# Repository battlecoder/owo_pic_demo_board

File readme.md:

# OWO PIC Demo Board
This is a very simple demo board I designed around one of my favorite microcontrollers: The PIC 16F628A from Microchip.
I also wrote a small "framework" in asm for it, that handles the display, buttons, serial comm, text scrolling, etc, and I've included a simple implementation of Tetris as an example of its usage.

You'll find the schematic and board layout (KiCad) of the *OWO board* in the **/board** folder. There's a lot that can be improved but it works as it is. The demo code and framework/boilerplate is in the **/asm_demo_code** directory.

You can see a video of one the early builds of the Tetris demo running on the board:
<blockquote class="twitter-tweet"><p lang="en" dir="ltr">Tetris implemented in assembly on the PIC16F628A demo board I designed a few months ago. <a href="https://twitter.com/hashtag/electronics?src=hash&amp;ref_src=twsrc%5Etfw">#electronics</a> <a href="https://twitter.com/hashtag/DIY?src=hash&amp;ref_src=twsrc%5Etfw">#DIY</a> <a href="https://twitter.com/hashtag/assemblycode?src=hash&amp;ref_src=twsrc%5Etfw">#assemblycode</a> <a href="https://twitter.com/hashtag/microchip?src=hash&amp;ref_src=twsrc%5Etfw">#microchip</a><br><a href="https://t.co/Uh5Tp1Ro5d"></img></a></p>&mdash; Elias Zacarias (@battlecoder)<a href="https://twitter.com/battlecoder/status/1109868608677707781?ref_src=twsrc%5Etfw">March 24, 2019</a></blockquote>

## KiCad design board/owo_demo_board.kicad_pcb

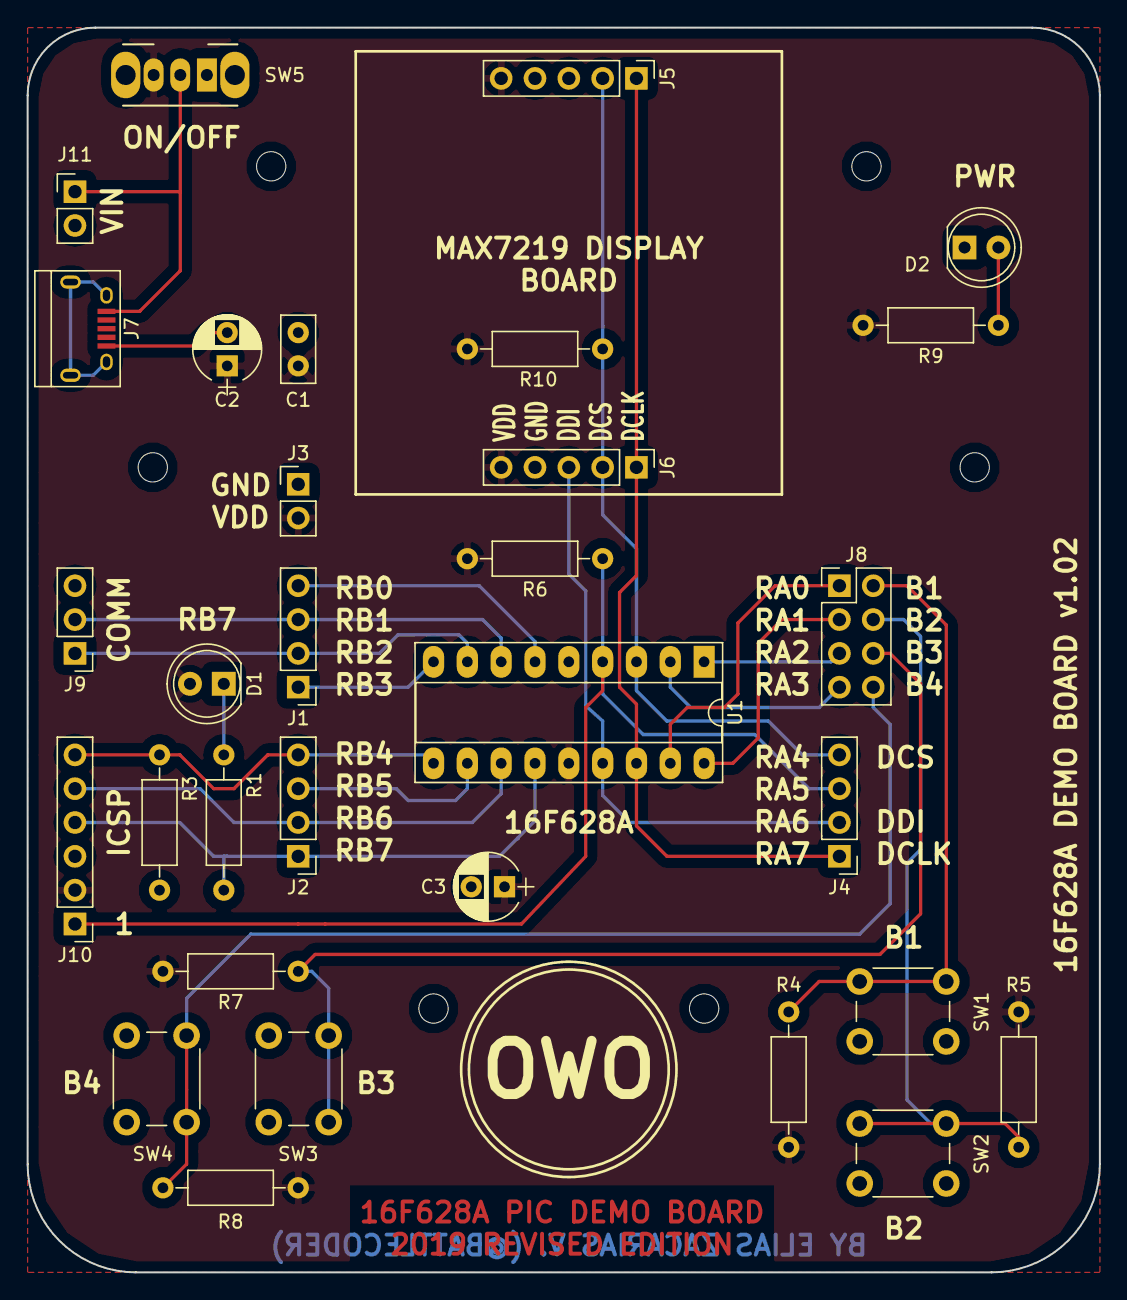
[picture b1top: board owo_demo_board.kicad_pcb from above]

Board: 2 copper layers, 80.5 x 93.5 mm, 31 parts (0 on the bottom side), 25 nets.

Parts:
C1: 0.1uF; C_Disc_D5.0mm_W2.5mm_P2.50mm
C2: 10uF; CP_Radial_D5.0mm_P2.50mm
C3: 1uF; CP_Radial_D5.0mm_P2.50mm
D1, D2: LED; LED_D5.0mm
J1: RB0-3; Pin_Header_Straight_1x04_Pitch2.54mm
J2: RB4-7; Pin_Header_Straight_1x04_Pitch2.54mm
J3: PWR_CONN; Pin_Header_Straight_1x02_Pitch2.54mm
J4: RA4-7; Pin_Header_Straight_1x04_Pitch2.54mm
J5: DISPLAY_1; Pin_Header_Straight_1x05_Pitch2.54mm
J6: DISPLAY_2; Pin_Header_Straight_1x05_Pitch2.54mm
J7: USB_OTG; USB_Micro-B
J8: CONN_02X04; Pin_Header_Straight_2x04_Pitch2.54mm
J9: COMM; Pin_Header_Straight_1x03_Pitch2.54mm
J10: ICSP; Pin_Header_Straight_1x06_Pitch2.54mm
J11: VIN; Pin_Header_Straight_1x02_Pitch2.54mm
R1: 4K7; R_Axial_DIN0207_L6.3mm_D2.5mm_P10.16mm_Horizontal
R3, R4, R5, R6, R7, R8, R10: 10K; R_Axial_DIN0207_L6.3mm_D2.5mm_P10.16mm_Horizontal
R9: 330; R_Axial_DIN0207_L6.3mm_D2.5mm_P10.16mm_Horizontal
SW1: B1; SW_PUSH_6mm
SW2: B2; SW_PUSH_6mm
SW3: B3; SW_PUSH_6mm
SW4: B4; SW_PUSH_6mm
SW5: SW_DPDT_x2; SW_CuK_OS102011MA1QN1_SPDT_Angled
U1: PIC16(L)F628A-I/P; DIP-18_W7.62mm_Socket_LongPads

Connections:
DIS_CLK: J4.1, J5.1, J6.1, U1.16
DIS_CS: J4.4, J5.2, J6.2, R10.1, U1.3
DIS_DI: J4.2, J6.3, U1.15
GND: C1.2, C2.2, C3.2, D2.1, J3.1, J5.4, J6.4, J7.5, J9.3, J10.3, J11.2, R3.1, SW1.2, SW2.2, SW3.2, SW4.2, U1.5
unnamed: D1.1, R1.2
unnamed: D2.2, R9.1
unnamed: J8.2, R4.1, SW1.1
unnamed: J8.4, R5.1, SW2.1
unnamed: J8.6, R7.1, SW3.1
unnamed: J8.8, R8.1, SW4.1
unnamed: J7.1, J11.1, SW5.2
RA0: J8.1, U1.17
RA1: J8.3, U1.18
RA2: J8.5, U1.1
RA3: J8.7, U1.2
RA5/_MCLR: J4.3, J10.1, R6.1, U1.4
RB0: J1.4, U1.6
RB1/RX: J1.3, J9.2, U1.7
RB2/TX: J1.2, J9.1, U1.8
RB3: J1.1, U1.9
RB4/PGM: J2.4, J10.6, R3.2, U1.10
RB5: J2.3, U1.11
RB6/PGC: J2.2, J10.5, U1.12
RB7/PGD: J2.1, J10.4, R1.1, U1.13
VDD: C1.1, C2.1, C3.1, D1.2, J3.2, J5.5, J6.5, J10.2, R4.2, R5.2, R6.2, R7.2, R8.2, R9.2, R10.2, SW5.3, U1.14

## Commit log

2019-05-13 Initial commit after cleanup
2019-05-13 Updated readme.md
    twitter embed.
2019-05-27 Added preview of the linked video in readme.md
